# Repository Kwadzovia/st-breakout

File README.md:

# st-breakout
STM32F070F6P6TR Breakout Board

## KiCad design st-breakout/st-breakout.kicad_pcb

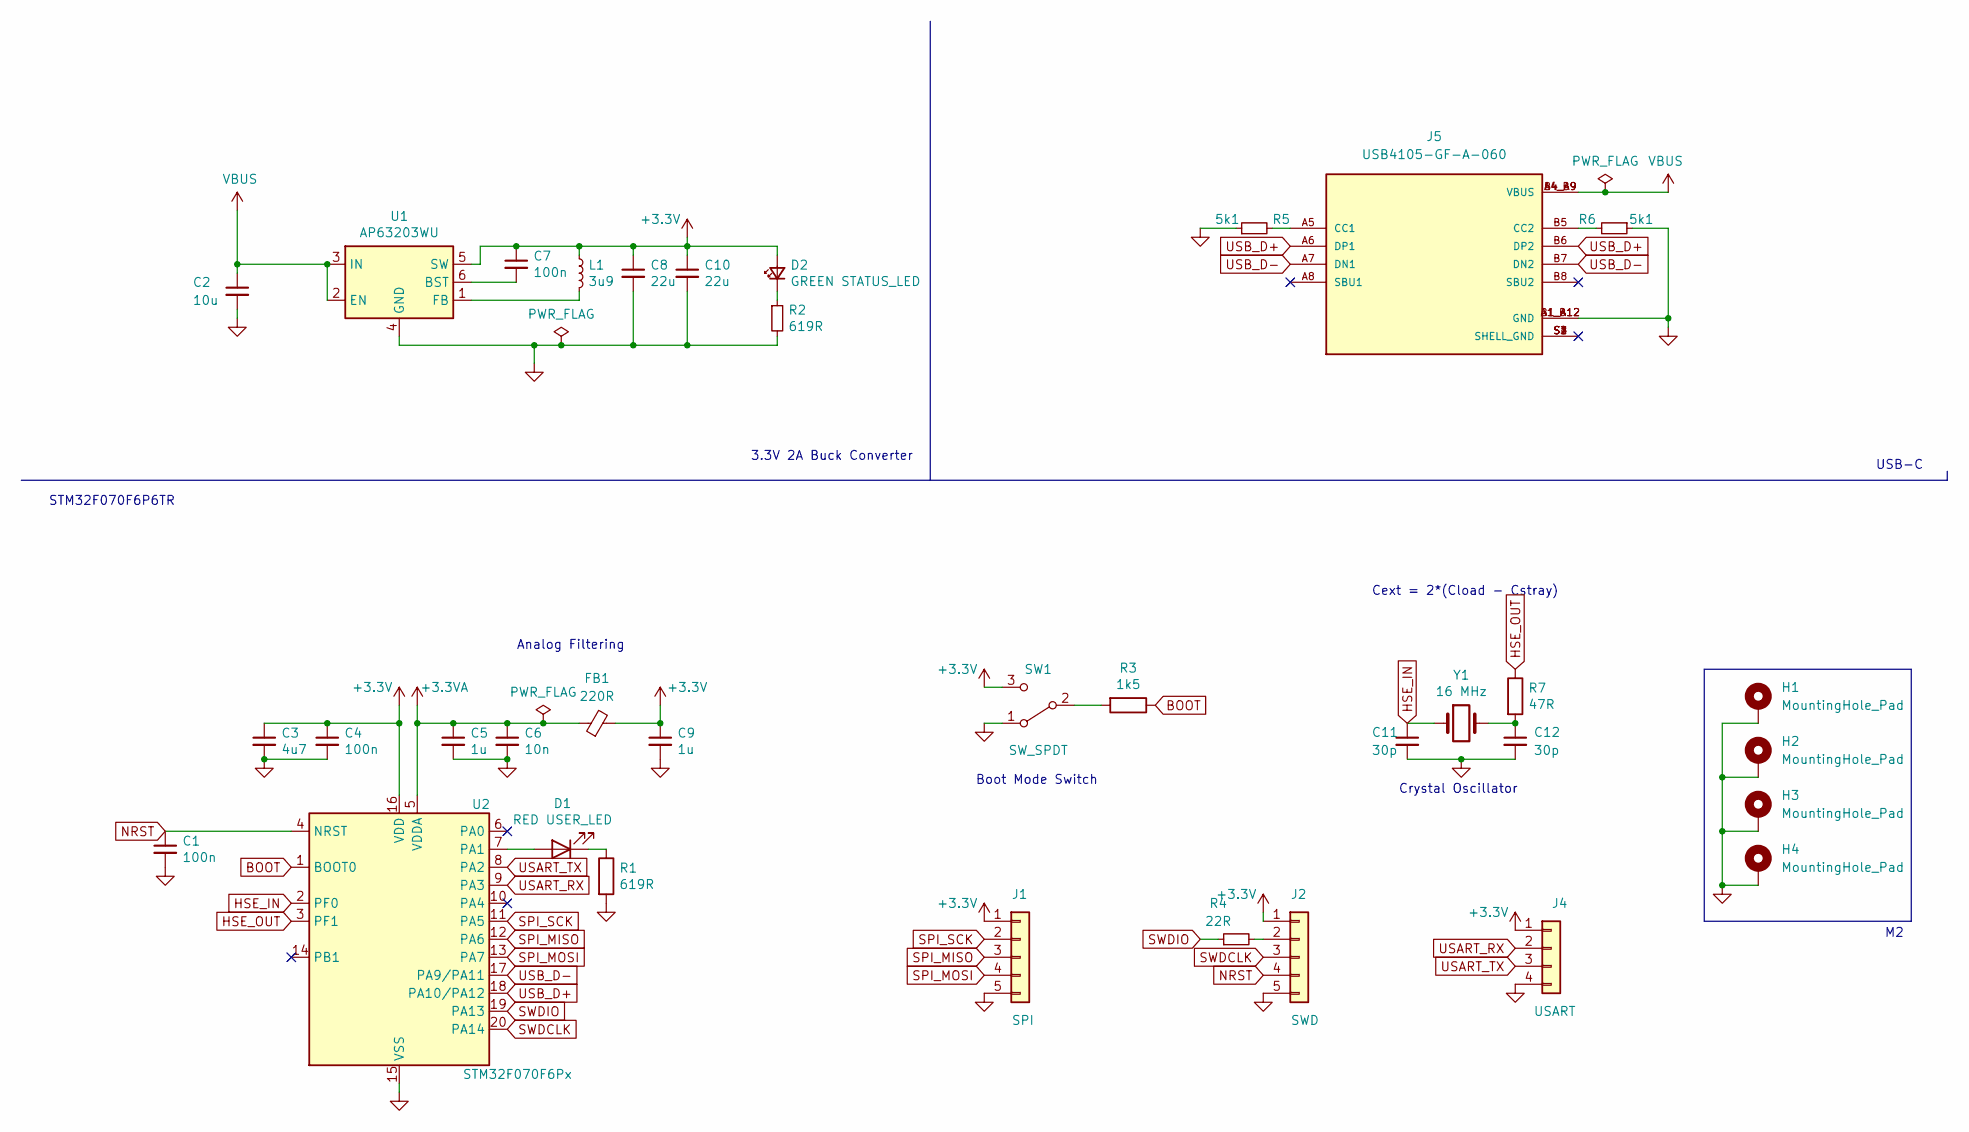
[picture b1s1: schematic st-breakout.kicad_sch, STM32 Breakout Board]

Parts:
C1, C4, C7: 100n; C_0402_1005Metric
C2: 10u; C_0603_1608Metric
C3: 4u7; C_0603_1608Metric
C5: 1u; C_0603_1608Metric
C6: 10n; C_0402_1005Metric
C8, C10: 22u; C_0805_2012Metric
C9: 1u; C_0402_1005Metric
C11, C12: 30p; C_0402_1005Metric
D1: RED USER_LED; LED_0603_1608Metric
D2: GREEN STATUS_LED; LED_0603_1608Metric
FB1: 220R; L_0603_1608Metric
H1, H2, H3, H4: MountingHole_Pad; MountingHole_2.5mm_Pad
J1: SPI; PinHeader_1x05_P2.54mm_Vertical
J2: SWD; PinHeader_1x05_P2.54mm_Vertical
J4: USART; PinHeader_1x04_P2.54mm_Vertical
J5: USB4105-GF-A-060; GCT_USB4105-GF-A-060; PARTREV A3
L1: 3u9; L_0603_1608Metric
R1, R2: 619R; R_0402_1005Metric
R3: 1k5; R_0402_1005Metric
R4: 22R; R_0402_1005Metric
R5, R6: 5k1; R_0402_1005Metric
R7: 47R; R_0402_1005Metric
SW1: SW_SPDT; SW_SPDT_PCM12
U1: AP63203WU; TSOT-23-6
U2: STM32F070F6Px; TSSOP-20_4.4x6.5mm_P0.65mm
Y1: 16 MHz; Crystal_SMD_HC49-SD

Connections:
+3.3V: C3.1, C4.1, C7.1, C8.1, C9.1, C10.1, D2.2 (A), FB1.2, J1.1, J2.1, J4.1, L1.1, SW1.3 (C), U1.5 (SW), U2.16 (VDD)
+3.3VA: C5.1, C6.1, FB1.1, U2.5 (VDDA)
BOOT: R3.1, U2.1 (BOOT0)
GND: C1.2, C2.2, C3.2, C4.2, C5.2, C6.2, C8.2, C9.2, C10.2, C11.2, C12.2, H1.1, H2.1, H3.1, H4.1, J1.5, J2.5, J4.4, J5.A1_B12 (GND), J5.B1_A12 (GND), R1.2, R2.2, R5.1, R6.1, SW1.1 (A), U1.4 (GND), U2.15 (VSS)
HSE_IN: C11.1, U2.2 (PF0), Y1.1
HSE_OUT: R7.1, U2.3 (PF1)
NRST: C1.1, J2.4, U2.4 (NRST)
unnamed: C12.1, R7.2, Y1.2
unnamed: D1.2 (A), U2.7 (PA1)
unnamed: D1.1 (K), R1.1
unnamed: D2.1 (K), R2.1
unnamed: J2.2, R4.2
unnamed: J5.A5 (CC1), R5.2
unnamed: J5.B5 (CC2), R6.2
unnamed: J5.S1 (SHELL_GND), J5.S2 (SHELL_GND), J5.S3 (SHELL_GND), J5.S4 (SHELL_GND)
unnamed: R3.2, SW1.2 (B)
unnamed: C7.2, U1.6 (BST)
unnamed: L1.2, U1.1 (FB)
SPI_MISO: J1.3, U2.12 (PA6)
SPI_MOSI: J1.4, U2.13 (PA7)
SPI_SCK: J1.2, U2.11 (PA5)
SWDCLK: J2.3, U2.20 (PA14)
SWDIO: R4.1, U2.19 (PA13)
USART_RX: J4.2, U2.9 (PA3)
USART_TX: J4.3, U2.8 (PA2)
USB_D+: J5.A6 (DP1), J5.B6 (DP2), U2.18 (PA10/PA12)
USB_D-: J5.A7 (DN1), J5.B7 (DN2), U2.17 (PA9/PA11)
VBUS: C2.1, J5.A4_B9 (VBUS), J5.B4_A9 (VBUS), U1.2 (EN), U1.3 (IN)

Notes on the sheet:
Analog Filtering
Crystal Oscillator
USB-C
STM32F070F6P6TR
Boot Mode Switch
Cext = 2*(Cload - Cstray)
3.3V 2A Buck Converter

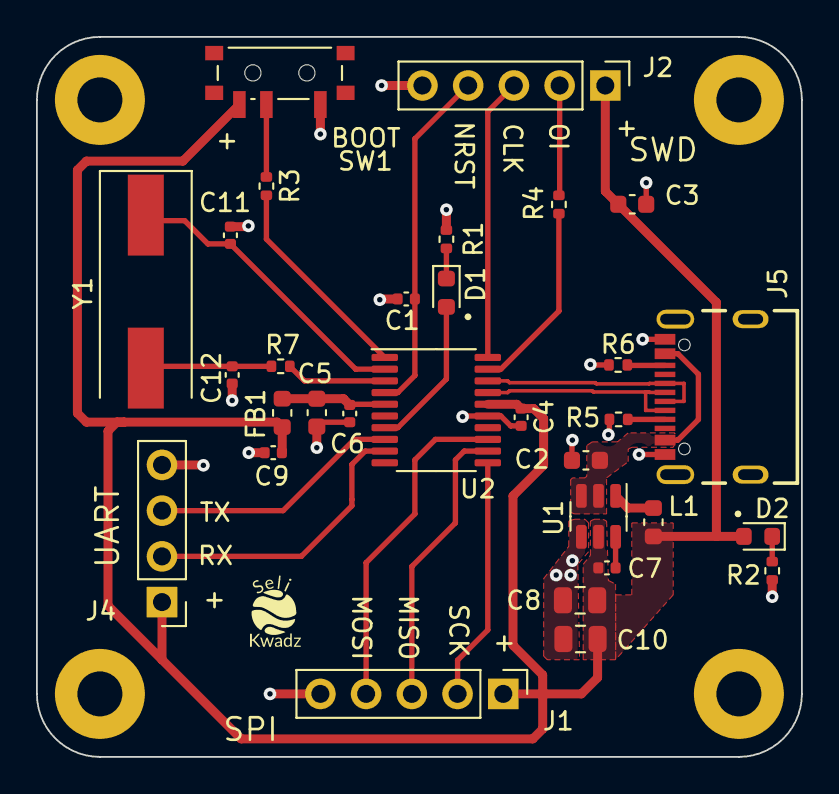
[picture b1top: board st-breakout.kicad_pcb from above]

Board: 2 copper layers, 42.5 x 40.0 mm, 35 parts (0 on the bottom side), 28 nets.

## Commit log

2023-05-24 Pinout and MCU schematic draft
2023-05-29 Change MCU model, Fill schematic and footprints
2023-06-11 routing and gerber
2023-06-11 regenerate with diode directions
